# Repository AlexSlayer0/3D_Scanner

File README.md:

# 3D_Scanner

Diplomarbeit HTL-Anichstraße
By Felix Granegger & Alexander Schiechtl

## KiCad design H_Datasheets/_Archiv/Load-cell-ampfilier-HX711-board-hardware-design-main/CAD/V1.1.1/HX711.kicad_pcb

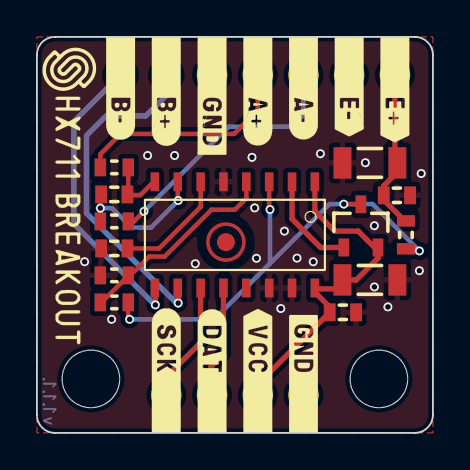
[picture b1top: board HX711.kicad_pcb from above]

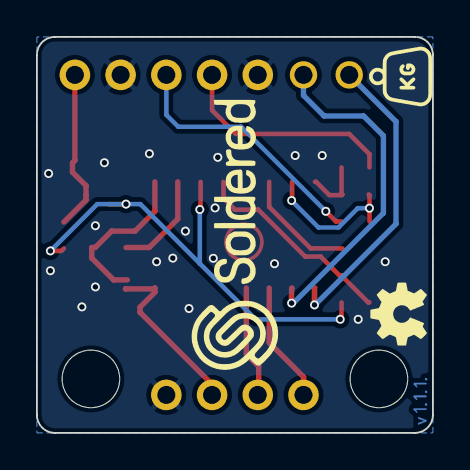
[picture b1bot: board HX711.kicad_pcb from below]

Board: 2 copper layers, 22.0 x 22.0 mm, 19 parts (3 on the bottom side), 15 nets.

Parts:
C1, C3, C4, C5: 100nF; 0603C
C2, C6: 10uF; 1206C
FD1: FIDUCIAL; FIDUCIAL_23
H1, H2: HOLE_3.2mm
K1: HEADER_MALE_5X1
K2: HEADER_MALE_2X1
K3: HEADER_MALE_4X1
Q1: MMBT4403; SOT-23-3
R1, R2: 100R; 0603R
R3: 20k; 0603R
R4: 8.2k; 0603R
R5: 10R; 0603R
U1: HX711; SOP-16

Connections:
GND: C1.1, C2.1, C3.1, C5.1, C6.1, K1.1, K1.4, K3.4, R4.1, U1.5 (AGND), U1.14 (XI), U1.15 (RATE)
unnamed: C1.2, C2.2, K1.5, R5.2
unnamed: C3.2, U1.6 (VBG)
unnamed: C4.1, R2.1, U1.8 (INPA+)
unnamed: C4.2, R1.1, U1.7 (INNA-)
unnamed: K1.2, R2.2
unnamed: K1.3, R1.2
unnamed: K2.1, U1.9 (INNB-)
unnamed: K2.2, U1.10 (INPB+)
unnamed: K3.1, U1.11 (PD_SCK)
unnamed: K3.2, U1.12 (DOUT)
unnamed: Q1.1 (B), U1.2 (BASE)
unnamed: Q1.3 (C), R3.2, R5.1, U1.3 (AVDD)
unnamed: R3.1, R4.2, U1.4 (VFB)
VCC: C5.2, C6.2, K3.3, Q1.2 (E), U1.1 (VSUP), U1.16 (DVDD)

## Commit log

2025-09-22 Altium_General_v1
    - Altium Leitner Template
    - Project RaspberryPi Ein- / Ausschaltung
2025-09-22 Altium v1.1
    Library Start
2025-09-29 ALtium
2025-09-29 Create Barcode_v01.py
    Barcode_v01 zum testen der GUI und weiterem
2025-10-04 Add 3D_Scanner library and update Raspberry project
    Added the 3D_Scanner.SchLib schematic library and its history files. Updated the Raspberry.PrjPcb project to include the new library, and made related changes to schematic documents and previews. Als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
2025-10-04 Add initial Altium project and schematic files
    Added the main Altium Designer project file, project structure, and all associated schematic documents for the 3D scanner project, including Kameras, Raspberry, Versorgung, and TOP sheets. Also inclu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
2025-10-06 Add Beleuchtung and Waage schematics, update project structure
    Added new schematic documents Beleuchtung.SchDoc and Waage.SchDoc, along with their previews. Updated 3D_Scanner_Gesamt.PrjPcb and 3D_Scanner_Gesamt.PrjPcbStructure to include these new sheets and ad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
2025-10-06 Barcode_File
    Restliche Barcode Files für bessere verständigung und weitere erklärung wie Yolo model zum herunterladen
2025-10-06 Interface_v06 hinzugefügt
    Neuste Version der GUI mit Foto anzeige
2025-10-06 Bemasung der Images - umramung
    Alle Python files wie beispiel Bilder die zeigen wie das objekt aussieht mit grüner umrandungslinie mit der entsprechenden größe
2025-10-07 Remove harness files and update schematics
    Deleted Kameras.Harness and Raspberry.Harness files and removed their references from the project file. Updated multiple schematic documents and previews, and added new history archives for version t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
2025-10-07 Kommunikation zwischen Skripte getestet
    Hier sind einige python Files um zu testen wie die Kommunikation zwischend en Skripten erfolgt über RAM
2025-10-07 USB-Kamera-getsetet
    Die Funktion einer USB-Kmaera getestet wie sia ngesteurt wird über python um fotos aufzunehmen
2025-10-07 Bemassung-ergänzt
    Es haben irgentwie python skripte gefehlt die nicht hochgeladen wurden
2025-10-14 Update Altium schematics and history files
    Removed outdated history files and added new versions for TOP, Versorgung, and Waage schematics. Updated main schematic documents and previews for 3D_Scanner_Gesamt. Added new RPI_Versorgung test pro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
2025-10-25 Prototyp_GUI
    kurze Zusammenfassung der teil Codes um die Funktion miteinander zu testen.
2025-10-27 Update Altium schematics and add depth test
    Replaced and added new history versions for multiple Altium schematic files (Kameras, Raspberry, TOP, Versorgung, Waage). Updated main schematic and preview files. Added Tiefenmessung_Test.py and mob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
2025-11-03 Add IRLZ44N library and update Altium project
    Added IRLZ44N.IntLib to the Libraries folder and referenced it in the 3D_Scanner_Gesamt project. Updated schematic documents and previews for Raspberry, TOP, and Versorgung. Cleaned up and refreshed 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
2025-11-03 Add HTLinn-Lib libraries and MOSFET test projects
    Added multiple new Altium integrated libraries (HTLinn-Lib) for RLC, BJT, Diode, FET, Logic, Miscellaneous, OPV, Opto, PowerSupply, and Sources, including device models and documentation. Also added 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
2025-11-04 Add IRLZ44N MOSFET library and update schematics
    Added IRLZ44N.SchLib and simulation/model files to the Libraries folder. Updated 3D_Scanner_Gesamt project to reference the new library. Modified multiple schematic documents and previews, and manage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
2025-11-05 Prototyp Aktualisieren
2025-11-05 Organisation/Kommunikation Aktualisieren
2025-11-05 Kameras Aktualisieren
2025-11-05 Bemassung Aktualisieren
2025-11-05 Barcodes Aktualisieren
2025-11-05 Bemassung_01
2025-11-05 Prototyp aktualisiert
2025-11-18 Add new libraries and update Altium project files
    Added several new integrated libraries to the Altium Libraries directory and updated the 3D_Scanner_Gesamt project to reference the new 2717.IntLib. Updated multiple schematic documents and their pre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
2025-11-18 Verbessere Lade-Dialog: Größe angepasst und Status-Text hinzugefügt
2025-11-18 Refactor camera handling: Implement CameraManager class for improved image capture and error handling
2025-11-18 Refactor GUI code for improved structure and readability; added loading dialog and enhanced image processing features
2025-11-18 Interface_v08
2026-01-12 Refactor depth camera measurement script to include a VirtualPlane class
2026-01-12 Add depth measurement scripts with object detection and ROI configuration
2026-01-12 Installation Tipps for the deth Camera
2026-01-20 Appending 3D Objects
2026-01-20 Altium updated
2026-01-20 Add Firmware
2026-01-20 Doku Start
2026-01-22 v08 ist nun fertig
2026-01-25 PythonFiles - Gewicht
2026-01-26 various objects
2026-01-27 commiten zum synchen
2026-01-27 Gewichtsmessung implementiert!!
2026-01-28 Implement optimized barcode detection and depth measurement modules
    - Added `BarCode_v03.py` for improved barcode detection using YOLO and pyzbar.
    - Introduced `Tiefenkamera_Messung_03.py` for depth measurement with DepthAI, including object segmentation and measurement calculations.
    - Enhanced logging for error handling and detection feedback.
    - Refactored image processing methods for better performance and accuracy.
    - Added main function `detect_barcodes` to facilitate barcode detection from a list of images.
2026-01-31 Status Buttons
2026-02-02 Doku
2026-02-02 Enhance barcode widget with delete functionality and improve camera check dialog
2026-02-02 Refactor camera management and improve camera check dialog for better usability
2026-02-02 Update Tiefenkamera und GUI
2026-02-03 Anbassungen für Parralellworker
2026-02-03 pcb_output
2026-02-03 Für Alex
    dsd
2026-02-03 Tiefenkamera geht mit XLink
2026-02-05 Add new scanner features
2026-02-10 Tiefenkamera mehrere Optionen zum Testen
2026-02-11 Flowchart
2026-02-12 Update .gitignore, enhance documentation, and modify log files for improved clarity and functionality
2026-02-12 Synch
2026-02-12 synch for laptop
2026-02-12 Tiefenkamera_v04 für raspy
2026-02-12 für raspy
2026-02-14 Doku_weiter
2026-02-14 Doku_Update
2026-02-15 Doku_Alex
    15.02.2026
2026-02-17 Tiefenkamere fertig
2026-02-18 OAK Foto implementiert mit Barcode testung erfolgreich und ediable Abmessungeb wie weight
2026-02-19 Update Doku
2026-02-19 Refactor translation management and enhance UI elements
    - Updated the TranslationManager class to include more structured translations for various UI components, including buttons, instructions, and status messages in German, English, and Italian.
    - Adjusted the maximum size instruction from 50x50x50 cm to 30x30x30 cm.
    - Added new sections for photo selection, overview, storage options, and calibration dialogs.
    - Removed the obsolete calibration.json file and introduced a new distanz_calibration.json file for distance calibration data.
    - Improved camera check and depth camera calibration processes with enhanced user feedback and progress dialogs.
    - Cleaned up the Tiefenkamera_Messung_02.py w
2026-02-23 Altium + Doku
2026-02-23 Für Alex
2026-02-23 Structure_Update
2026-02-23 Anpassungen Struktur
2026-02-23 Struktur
2026-02-23 Distanzmeassurement wurde ganz hinzugefügt - Kleinlichkeiten fehlen
2026-02-23 Prototyp funktioniert gewaltig - mit test für Alex Tiefenkamera
2026-02-23 Test Alex für 3D-Scanner
2026-02-24 Für Alex Testung mit Tiefenkamera
2026-02-24 Doku Update
2026-02-26 Doku Alex
2026-02-26 OneNote
2026-03-03 Offset bei ROI Fenster
2026-03-03 final worker anpassungen
2026-03-03 GUI mit workers aktualisiert auf den neusten Stand
2026-03-04 Gewichtmessung auf 20 mal wiederholt - Kleine anpassungen bei distanz - DOKU mit Tiefenkamera Bilder
2026-03-05 Doku Alex Update
2026-03-07 Doku Update Alex
2026-03-09 OutputJob + bissle Doku
2026-03-09 Fehler bei der volume Fehlermeldung
2026-03-10 Barcodes dokumentiert
2026-03-11 licht für den gesamt durchlauf angeschalten und bei Wiederholung auch anschalten
2026-03-11 control_light angepasst an die Funktion vom Camera manager
2026-03-11 Bilder werden immer korrekt angezeigt auch nach rebeginn
2026-03-11 g in kg umrechnung bei der anzeige weil es in kg in das SAP eingetragen wird
2026-03-11 logging anpassen
2026-03-11 Doku Update - Felix
2026-03-12 gitignore update
2026-03-12 updatet gitignore
2026-03-13 Doku Korrekturen etc.
2026-03-14 Doku Update und Barcode update
2026-03-16 Restart bei Startseite zurück
2026-03-16 Gewichts Kalibrierung und Lichtsteuerung und STartseiten Skalierungs fixx
2026-03-16 pip install libarys hinzugefügt - mit doku hinzugefügt
2026-03-16 CSV Formatierung
2026-03-19 Ka irgend a update oder so
2026-03-19 Doku - Gewichtsmessung mit Logger erweitert
2026-03-20 alles auf left umgestellt
2026-03-22 Bug fixx
2026-03-23 Benutzerhandbuch hinzugefügt
2026-03-23 kleiner fix
2026-03-24 Richtig umbennenung von distnaz_measure
